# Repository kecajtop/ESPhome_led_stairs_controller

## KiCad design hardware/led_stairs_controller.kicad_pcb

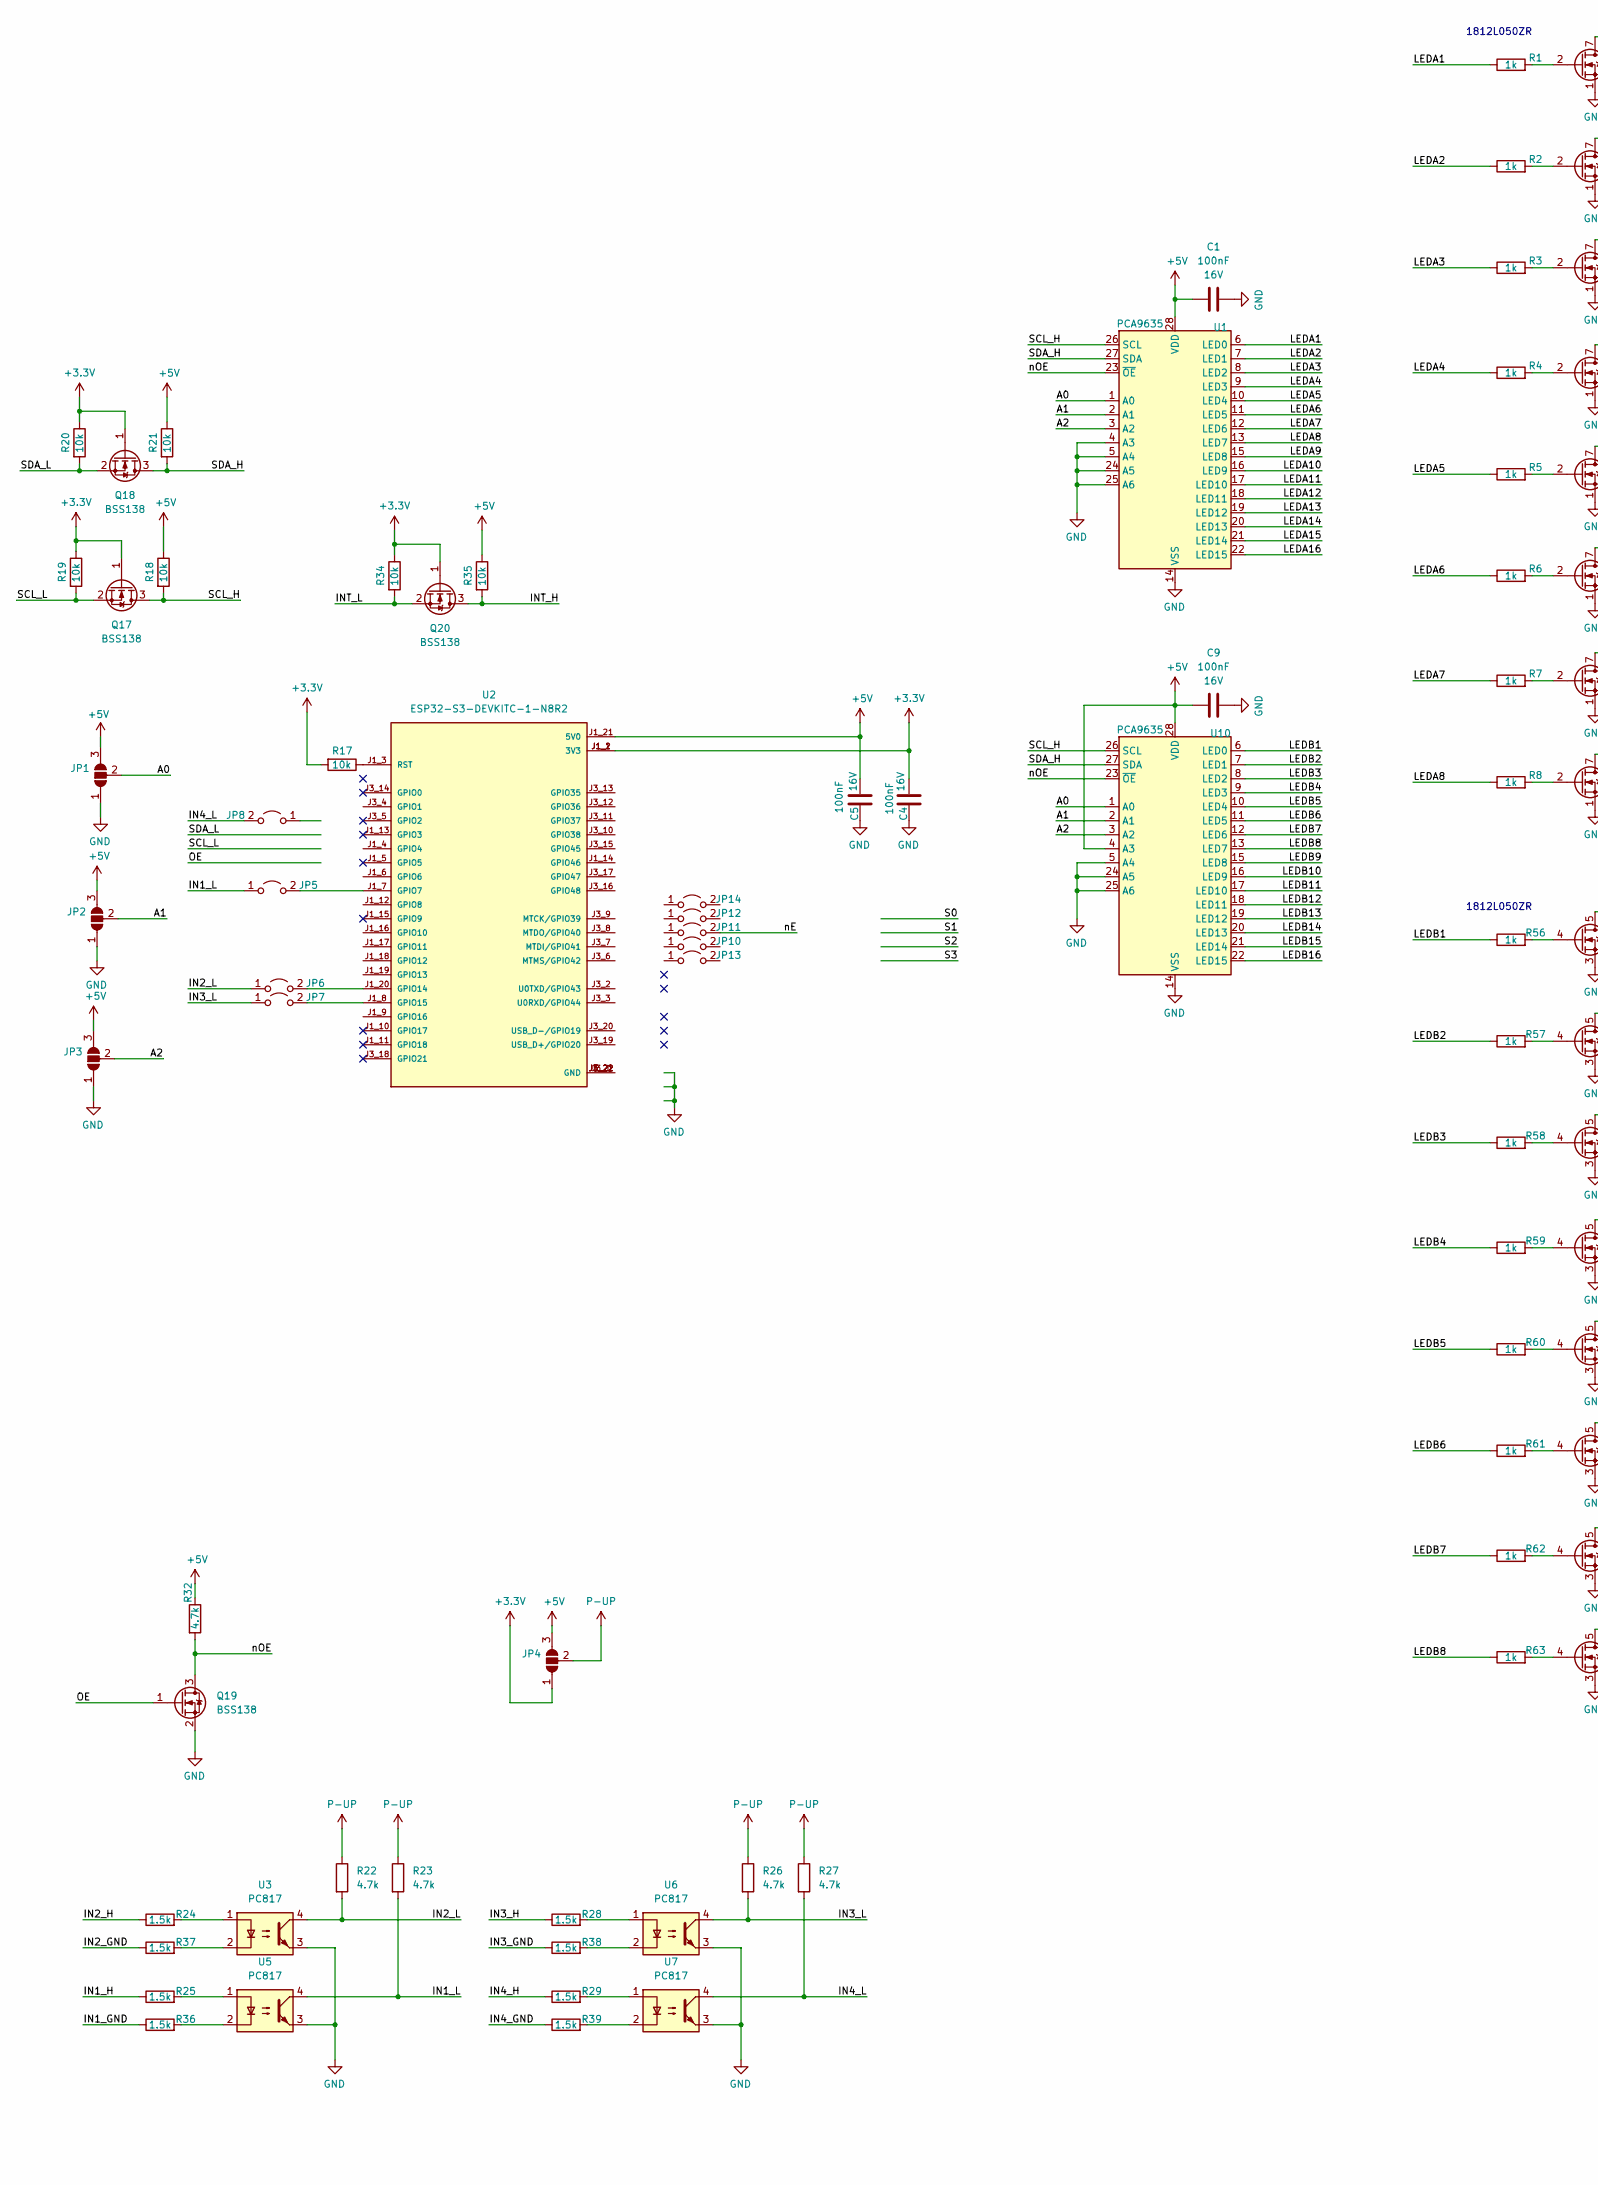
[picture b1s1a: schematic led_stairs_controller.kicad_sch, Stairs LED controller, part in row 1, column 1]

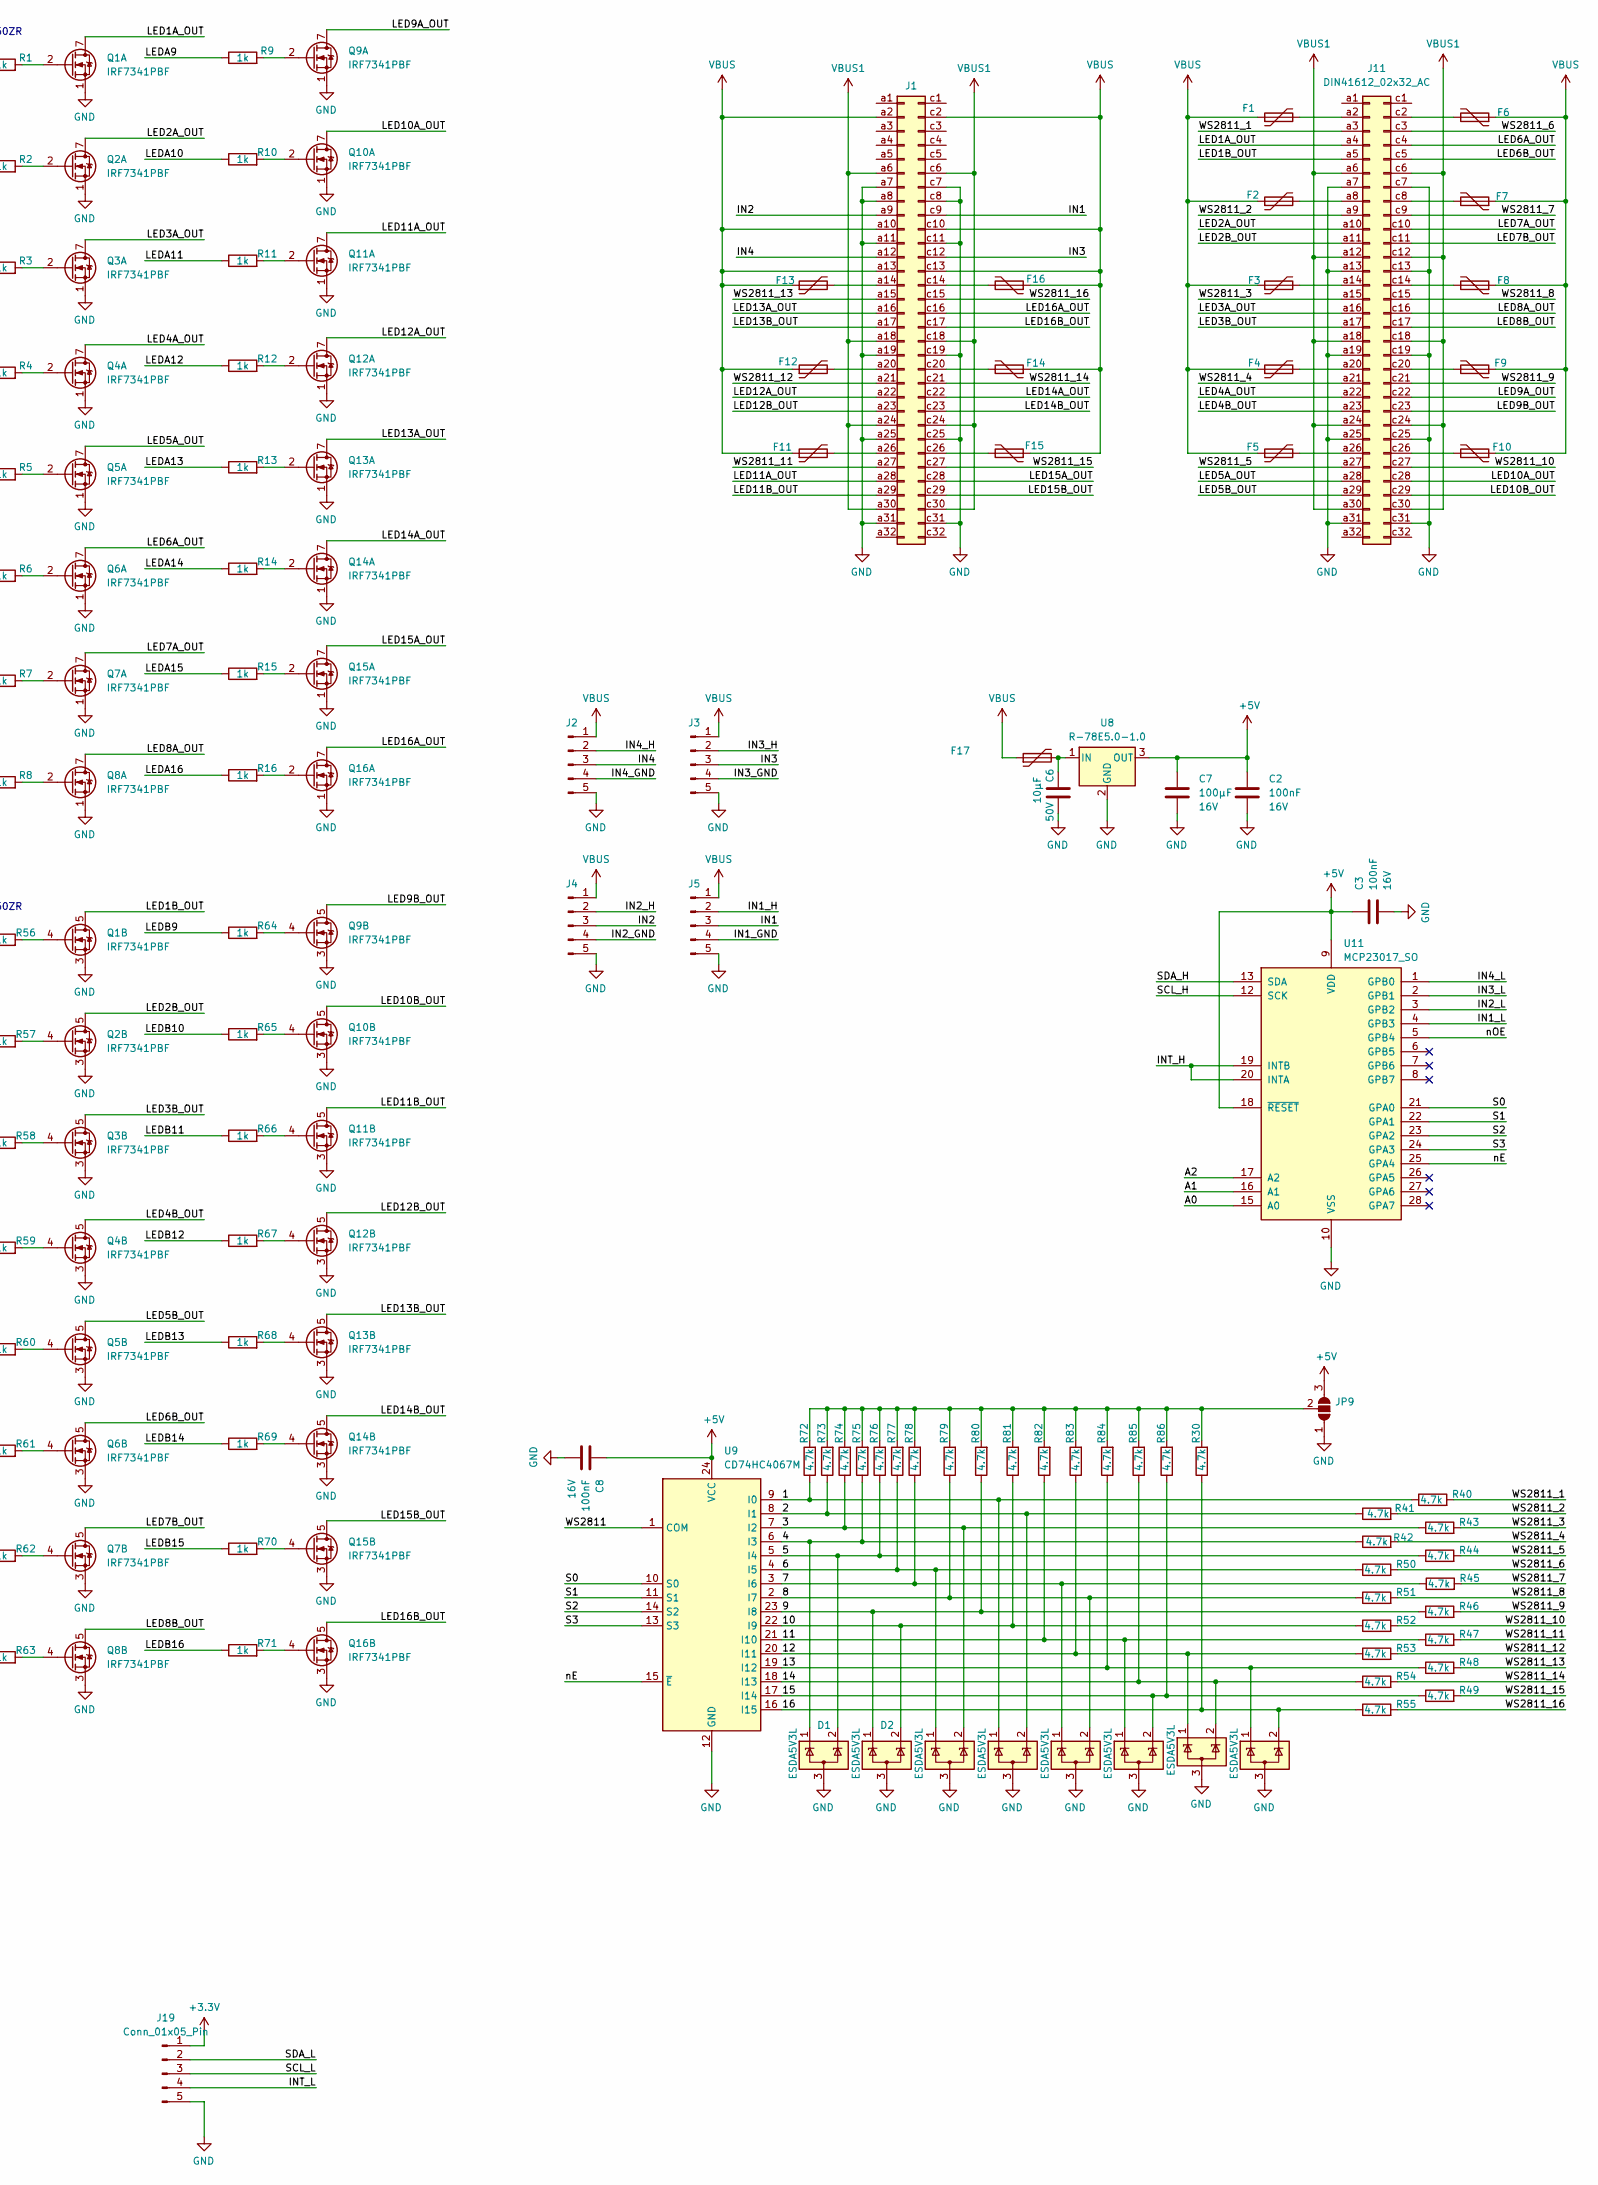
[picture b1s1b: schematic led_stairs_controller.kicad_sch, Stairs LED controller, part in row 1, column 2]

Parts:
C1, C2, C3, C4, C5, C8, C9: C0603_100nF_16V_X7R; C_0603_1608Metric; Voltage 16V; Manufacturer Part Number C0603C104J4RACTU; LCSC C14663
C6: C1210_10µF_50V_X5R; C_1210_3225Metric; Voltage 50V; Manufacturer Part Number C1210C106K5PAC7210; LCSC C13585
C7: C1210_100µF_16V_X5R; C_1210_3225Metric; Voltage 16V; Manufacturer Part Number C1210C107M4PAC7800; LCSC C15008
D1, D2, D3, D4, D5, D6, D7, D8: ESDA5V3L; SOT-23-3; LCSC C968007
F1, F2, F3, F4, F5, F6, F7, F8, F9, F10, F11, F12, F13, F14, F15, F16, F17: Polyfuse; Fuse_1812_4532Metric; LCSC C142747
J1, J11: DIN41612_02x32_AC; DIN41612_C_2x32_Male_Horizontal_THT
J2, J3, J4, J5: Conn_01x05_Pin; Jumper 5
J19: Conn_01x05_Pin; PinHeader_1x05_P2.54mm_Vertical
JP1, JP2, JP3, JP4, JP9: SolderJumper_3_Open; SolderJumper-3_P1.3mm_Open_RoundedPad1.0x1.5mm_NumberLabels
JP5, JP6, JP7, JP8, JP10, JP11, JP12, JP13, JP14: Jumper_2_Open; SolderJumper-2_P1.3mm_Open_RoundedPad1.0x1.5mm
Q1, Q2, Q3, Q4, Q5, Q6, Q7, Q8, Q9, Q10, Q11, Q12, Q13, Q14, Q15, Q16: IRF7341PBF; SOIC-8_3.9x4.9mm_P1.27mm
Q17, Q18, Q19, Q20: BSS138; SOT-23; LCSC C8545
R1, R2, R3, R4, R5, R6, R7, R8, R9, R10, R11, R12, R13, R14, R15, R16, R56, R57, R58, R59, R60, R61, R62, R63, R64, R65, R66, R67, R68, R69, R70, R71: R0603_1k_1%_100mW_100PPM_AC; R_0603_1608Metric; Manufacturer Part Number AC0603FR-071KL; LCSC C21190
R17, R18, R19, R20, R21, R34, R35: R0603_10k_1%_100mW_100PPM_AC; R_0603_1608Metric; Manufacturer Part Number AC0603FR-0710KL; LCSC C25804
R22, R23, R26, R27, R30, R32, R40, R41, R42, R43, R44, R45, R46, R47, R48, R49, R50, R51, R52, R53, R54, R55, R72, R73, R74, R75, R76, R77, R78, R79, R80, R81, R82, R83, R84, R85, R86: R0603_4.7k_1%_100mW_100PPM_AC; R_0603_1608Metric; Manufacturer Part Number AC0603FR-074K7L; LCSC C23162
R24, R25, R28, R29, R36, R37, R38, R39: R0805_1.5k_1%_125mW_100PPM_AC; R_0805_2012Metric; Manufacturer Part Number AC0805FR-071K5L; LCSC C22843
U1, U10: PCA9635; TSSOP-28_4.4x9.7mm_P0.65mm; LCSC C110795
U2: ESP32-S3-DEVKITC-1-N8R2; XCVR_ESP32-S3-DEVKITC-1-N8R2; PARTREV V1
U3, U5, U6, U7: PC817; DIP-4_W7.62mm; LCSC C109225
U8: R-78E5.0-1.0; Converter_DCDC_RECOM_R-78E-0.5_THT
U9: CD74HC4067M; SOIC-24W_7.5x15.4mm_P1.27mm
U11: MCP23017_SO; SOIC-28W_7.5x17.9mm_P1.27mm

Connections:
+3.3V: C4.1, J19.1, JP4.1 (A), Q17.1 (G), Q18.1 (G), Q20.1 (G), R17.2, R19.1, R20.1, R34.1, U2.J1_1 (3V3), U2.J1_2 (3V3)
+5V: C1.1, C2.2, C3.2, C5.1, C7.1, C8.2, C9.1, JP1.3 (B), JP2.3 (B), JP3.3 (B), JP4.3 (B), JP9.3 (B), R18.1, R21.1, R32.1, R35.1, U1.28 (VDD), U2.J1_21 (5V0), U8.3 (OUT), U9.24 (VCC), U10.4 (A3), U10.28 (VDD), U11.9 (VDD), U11.18 (~RESET)
/1: D4.1 (K), R40.1, R72.1, U9.9 (I0)
/2: D4.2 (K), R41.1, R73.1, U9.8 (I1)
/3: D3.2 (K), R43.1, R74.1, U9.7 (I2)
/4: D1.1 (K), R42.1, R75.1, U9.6 (I3)
/5: D1.2 (K), R44.1, R76.1, U9.5 (I4)
/6: D3.1 (K), R50.1, R77.1, U9.4 (I5)
/7: D5.1 (K), R45.1, R78.1, U9.3 (I6)
/8: D5.2 (K), R51.1, R79.1, U9.2 (I7)
/9: D2.1 (K), R46.1, R80.1, U9.23 (I8)
/10: D2.2 (K), R52.1, R81.1, U9.22 (I9)
/11: D6.1 (K), R47.1, R82.1, U9.21 (I10)
/12: D7.1 (K), R53.1, R83.1, U9.20 (I11)
/13: D8.1 (K), R48.1, R84.1, U9.19 (I12)
/14: D7.2 (K), R54.1, R85.1, U9.18 (I13)
/15: D6.2 (K), R49.1, R86.1, U9.17 (I14)
/16: D8.2 (K), R30.1, R55.1, U9.16 (I15)
/A0: JP1.2 (C), U1.1 (A0), U10.1 (A0), U11.15 (A0)
/A1: JP2.2 (C), U1.2 (A1), U10.2 (A1), U11.16 (A1)
/A2: JP3.2 (C), U1.3 (A2), U10.3 (A2), U11.17 (A2)
/IN1: J1.c9, J5.3
/IN1_GND: J5.4, R36.1
/IN1_H: J5.2, R25.1
/IN1_L: JP5.1 (A), R23.2, U5.4, U11.4 (GPB3)
/IN2: J1.a9, J4.3
/IN2_GND: J4.4, R37.1
/IN2_H: J4.2, R24.1
/IN2_L: JP6.1 (A), R22.2, U3.4, U11.3 (GPB2)
/IN3: J1.c12, J3.3
/IN3_GND: J3.4, R38.1
/IN3_H: J3.2, R28.1
/IN3_L: JP7.1 (A), R26.2, U6.4, U11.2 (GPB1)
/IN4: J1.a12, J2.3
/IN4_GND: J2.4, R39.1
/IN4_H: J2.2, R29.1
/IN4_L: JP8.2 (B), R27.2, U7.4, U11.1 (GPB0)
/INT_H: Q20.3 (D), R35.2, U11.19 (INTB), U11.20 (INTA)
/INT_L: J19.4, Q20.2 (S), R34.2
/LED1A_OUT: J11.a4, Q1.7 (D1), Q1.8 (D1)
/LED1B_OUT: J11.a5, Q1.5 (D2), Q1.6 (D2)
/LED2A_OUT: J11.a10, Q2.7 (D1), Q2.8 (D1)
/LED2B_OUT: J11.a11, Q2.5 (D2), Q2.6 (D2)
/LED3A_OUT: J11.a16, Q3.7 (D1), Q3.8 (D1)
/LED3B_OUT: J11.a17, Q3.5 (D2), Q3.6 (D2)
/LED4A_OUT: J11.a22, Q4.7 (D1), Q4.8 (D1)
/LED4B_OUT: J11.a23, Q4.5 (D2), Q4.6 (D2)
/LED5A_OUT: J11.a28, Q5.7 (D1), Q5.8 (D1)
/LED5B_OUT: J11.a29, Q5.5 (D2), Q5.6 (D2)
/LED6A_OUT: J11.c4, Q6.7 (D1), Q6.8 (D1)
/LED6B_OUT: J11.c5, Q6.5 (D2), Q6.6 (D2)
/LED7A_OUT: J11.c10, Q7.7 (D1), Q7.8 (D1)
/LED7B_OUT: J11.c11, Q7.5 (D2), Q7.6 (D2)
/LED8A_OUT: J11.c16, Q8.7 (D1), Q8.8 (D1)
/LED8B_OUT: J11.c17, Q8.5 (D2), Q8.6 (D2)
/LED9A_OUT: J11.c22, Q9.7 (D1), Q9.8 (D1)
/LED9B_OUT: J11.c23, Q9.5 (D2), Q9.6 (D2)
/LED10A_OUT: J11.c28, Q10.7 (D1), Q10.8 (D1)
/LED10B_OUT: J11.c29, Q10.5 (D2), Q10.6 (D2)
/LED11A_OUT: J1.a28, Q11.7 (D1), Q11.8 (D1)
/LED11B_OUT: J1.a29, Q11.5 (D2), Q11.6 (D2)
/LED12A_OUT: J1.a22, Q12.7 (D1), Q12.8 (D1)
/LED12B_OUT: J1.a23, Q12.5 (D2), Q12.6 (D2)
/LED13A_OUT: J1.a16, Q13.7 (D1), Q13.8 (D1)
/LED13B_OUT: J1.a17, Q13.5 (D2), Q13.6 (D2)
/LED14A_OUT: J1.c22, Q14.7 (D1), Q14.8 (D1)
/LED14B_OUT: J1.c23, Q14.5 (D2), Q14.6 (D2)
/LED15A_OUT: J1.c28, Q15.7 (D1), Q15.8 (D1)
/LED15B_OUT: J1.c29, Q15.5 (D2), Q15.6 (D2)
/LED16A_OUT: J1.c16, Q16.7 (D1), Q16.8 (D1)
/LED16B_OUT: J1.c17, Q16.5 (D2), Q16.6 (D2)
/LEDA1: R1.1, U1.6 (LED0)
/LEDA2: R2.1, U1.7 (LED1)
/LEDA3: R3.1, U1.8 (LED2)
/LEDA4: R4.1, U1.9 (LED3)
/LEDA5: R5.1, U1.10 (LED4)
/LEDA6: R6.1, U1.11 (LED5)
/LEDA7: R7.1, U1.12 (LED6)
/LEDA8: R8.1, U1.13 (LED7)
/LEDA9: R9.1, U1.15 (LED8)
/LEDA10: R10.1, U1.16 (LED9)
/LEDA11: R11.1, U1.17 (LED10)
/LEDA12: R12.1, U1.18 (LED11)
/LEDA13: R13.1, U1.19 (LED12)
/LEDA14: R14.1, U1.20 (LED13)
/LEDA15: R15.1, U1.21 (LED14)
/LEDA16: R16.1, U1.22 (LED15)
/LEDB1: R56.1, U10.6 (LED0)
/LEDB2: R57.1, U10.7 (LED1)
/LEDB3: R58.1, U10.8 (LED2)
/LEDB4: R59.1, U10.9 (LED3)
/LEDB5: R60.1, U10.10 (LED4)
/LEDB6: R61.1, U10.11 (LED5)
/LEDB7: R62.1, U10.12 (LED6)
/LEDB8: R63.1, U10.13 (LED7)
/LEDB9: R64.1, U10.15 (LED8)
/LEDB10: R65.1, U10.16 (LED9)
/LEDB11: R66.1, U10.17 (LED10)
/LEDB12: R67.1, U10.18 (LED11)
/LEDB13: R68.1, U10.19 (LED12)
/LEDB14: R69.1, U10.20 (LED13)
/LEDB15: R70.1, U10.21 (LED14)
/LEDB16: R71.1, U10.22 (LED15)
/OE: Q19.1 (G)
/S0: U9.10 (S0), U11.21 (GPA0)
/S1: U9.11 (S1), U11.22 (GPA1)
/S2: U9.14 (S2), U11.23 (GPA2)
/S3: U9.13 (S3), U11.24 (GPA3)
/SCL_H: Q17.3 (D), R18.2, U1.26 (SCL), U10.26 (SCL), U11.12 (SCK)
/SCL_L: J19.3, Q17.2 (S), R19.2
/SDA_H: Q18.3 (D), R21.2, U1.27 (SDA), U10.27 (SDA), U11.13 (SDA)
/SDA_L: J19.2, Q18.2 (S), R20.2
/WS2811: U9.1 (COM)
/WS2811_1: J11.a3, R40.2
/WS2811_2: J11.a9, R41.2
/WS2811_3: J11.a15, R43.2
/WS2811_4: J11.a21, R42.2
/WS2811_5: J11.a27, R44.2
/WS2811_6: J11.c3, R50.2
/WS2811_7: J11.c9, R45.2
/WS2811_8: J11.c15, R51.2
/WS2811_9: J11.c21, R46.2
/WS2811_10: J11.c27, R52.2
/WS2811_11: J1.a27, R47.2
/WS2811_12: J1.a21, R53.2
/WS2811_13: J1.a15, R48.2
/WS2811_14: J1.c21, R54.2
/WS2811_15: J1.c27, R49.2
/WS2811_16: J1.c15, R55.2
/nE: JP11.2 (B), U9.15 (~E), U11.25 (GPA4)
/nOE: Q19.3 (D), R32.2, U1.23 (~OE), U10.23 (~OE), U11.5 (GPB4)
GND: C1.2, C2.1, C3.1, C4.2, C5.2, C6.2, C7.2, C8.1, C9.2, D1.3 (A), D2.3 (A), D3.3 (A), D4.3 (A), D5.3 (A), D6.3 (A), D7.3 (A), D8.3 (A), J1.a7, J1.a8, J1.a11, J1.a19, J1.a25, J1.a31, J1.c7, J1.c8, J1.c11, J1.c19, J1.c25, J1.c31, J2.5, J3.5, J4.5, J5.5, J11.a7, J11.a13, J11.a19, J11.a25, J11.a31, J11.c7, J11.c13, J11.c19, J11.c25, J11.c31, J19.5, JP1.1 (A), JP2.1 (A), JP3.1 (A), JP9.1 (A), Q1.1 (S1), Q1.3 (S2), Q2.1 (S1), Q2.3 (S2), Q3.1 (S1), Q3.3 (S2), Q4.1 (S1), Q4.3 (S2), Q5.1 (S1), Q5.3 (S2), Q6.1 (S1), Q6.3 (S2), Q7.1 (S1), Q7.3 (S2), Q8.1 (S1), Q8.3 (S2), Q9.1 (S1), Q9.3 (S2), Q10.1 (S1), Q10.3 (S2), Q11.1 (S1), Q11.3 (S2), Q12.1 (S1), Q12.3 (S2), Q13.1 (S1), Q13.3 (S2), Q14.1 (S1), Q14.3 (S2), Q15.1 (S1), Q15.3 (S2), Q16.1 (S1), Q16.3 (S2), Q19.2 (S), U1.4 (A3), U1.5 (A4), U1.14 (VSS), U1.24 (A5), U1.25 (A6), U3.3, U5.3, U6.3, U7.3, U8.2 (GND), U9.12 (GND), U10.5 (A4), U10.14 (VSS), U10.24 (A5), U10.25 (A6), U11.10 (VSS)
unnamed: F13.2, J1.a14
unnamed: F12.2, J1.a20
unnamed: F11.2, J1.a26
unnamed: F16.2, J1.c14
unnamed: F14.2, J1.c20
unnamed: F15.2, J1.c26
unnamed: F1.2, J11.a2
unnamed: F2.2, J11.a8
unnamed: F3.2, J11.a14
unnamed: F4.2, J11.a20
unnamed: F5.2, J11.a26
unnamed: F6.2, J11.c2
unnamed: F7.2, J11.c8
unnamed: F8.2, J11.c14
unnamed: F9.2, J11.c20
unnamed: F10.2, J11.c26
unnamed: JP5.2 (B), U2.J1_7 (GPIO7)
unnamed: JP6.2 (B), U2.J1_20 (GPIO14)
unnamed: JP7.2 (B), U2.J1_8 (GPIO15)
unnamed: JP9.2 (C), R30.2, R72.2, R73.2, R74.2, R75.2, R76.2, R77.2, R78.2, R79.2, R80.2, R81.2, R82.2, R83.2, R84.2, R85.2, R86.2
unnamed: Q1.2 (G1), R1.2
unnamed: Q1.4 (G2), R56.2
unnamed: Q2.2 (G1), R2.2
unnamed: Q2.4 (G2), R57.2
unnamed: Q3.2 (G1), R3.2
unnamed: Q3.4 (G2), R58.2
unnamed: Q4.2 (G1), R4.2
unnamed: Q4.4 (G2), R59.2
unnamed: Q5.2 (G1), R5.2
unnamed: Q5.4 (G2), R60.2
unnamed: Q6.2 (G1), R6.2
unnamed: Q6.4 (G2), R61.2
unnamed: Q7.2 (G1), R7.2
unnamed: Q7.4 (G2), R62.2
unnamed: Q8.2 (G1), R8.2
unnamed: Q8.4 (G2), R63.2
unnamed: Q9.2 (G1), R9.2
unnamed: Q9.4 (G2), R64.2
unnamed: Q10.2 (G1), R10.2
unnamed: Q10.4 (G2), R65.2
unnamed: Q11.2 (G1), R11.2
unnamed: Q11.4 (G2), R66.2
unnamed: Q12.2 (G1), R12.2
unnamed: Q12.4 (G2), R67.2
unnamed: Q13.2 (G1), R13.2
unnamed: Q13.4 (G2), R68.2
unnamed: Q14.2 (G1), R14.2
unnamed: Q14.4 (G2), R69.2
unnamed: Q15.2 (G1), R15.2
unnamed: Q15.4 (G2), R70.2
unnamed: Q16.2 (G1), R16.2
unnamed: Q16.4 (G2), R71.2
unnamed: R24.2, U3.1
unnamed: R25.2, U5.1
unnamed: R28.2, U6.1
unnamed: R29.2, U7.1
unnamed: R36.2, U5.2
unnamed: R37.2, U3.2
unnamed: R38.2, U6.2
unnamed: R39.2, U7.2
unnamed: R17.1, U2.J1_3 (RST)
unnamed: C6.1, F17.2, U8.1 (IN)
P-UP: JP4.2 (C), R22.1, R23.1, R26.1, R27.1
VBUS: F1.1, F2.1, F3.1, F4.1, F5.1, F6.1, F7.1, F8.1, F9.1, F10.1, F11.1, F12.1, F13.1, F14.1, F15.1, F16.1, F17.1, J1.a2, J1.a10, J1.a13, J1.c2, J1.c10, J1.c13, J2.1, J3.1, J4.1, J5.1
VBUS1: J1.a6, J1.a18, J1.a24, J1.a30, J1.c6, J1.c18, J1.c24, J1.c30, J11.a6, J11.a12, J11.a18, J11.a24, J11.a30, J11.c6, J11.c12, J11.c18, J11.c24, J11.c30

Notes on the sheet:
1812L050ZR

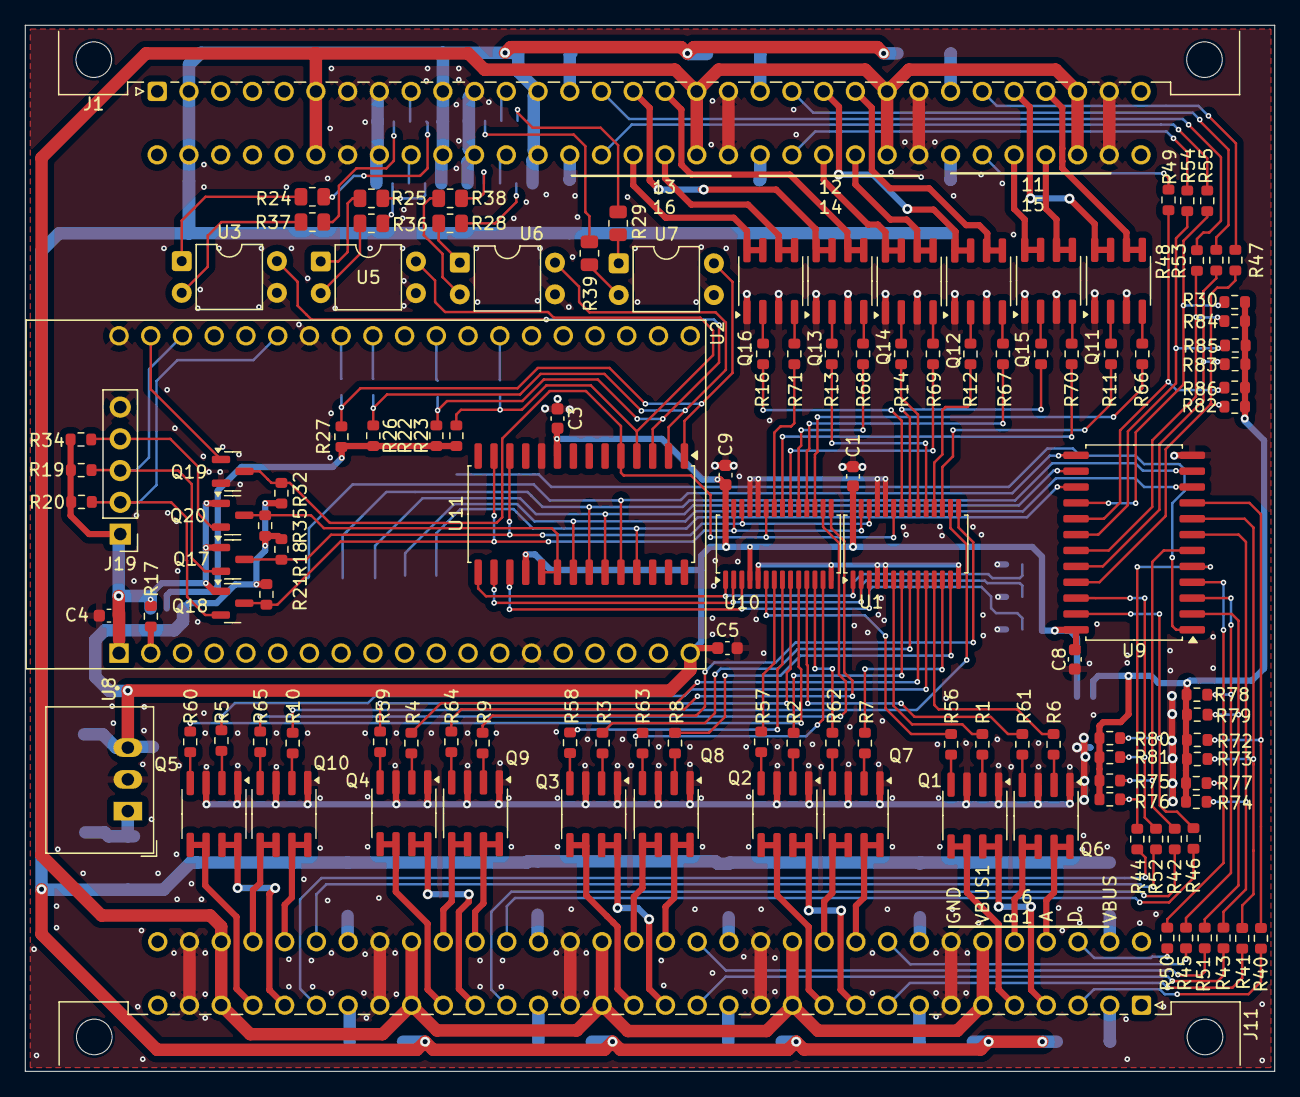
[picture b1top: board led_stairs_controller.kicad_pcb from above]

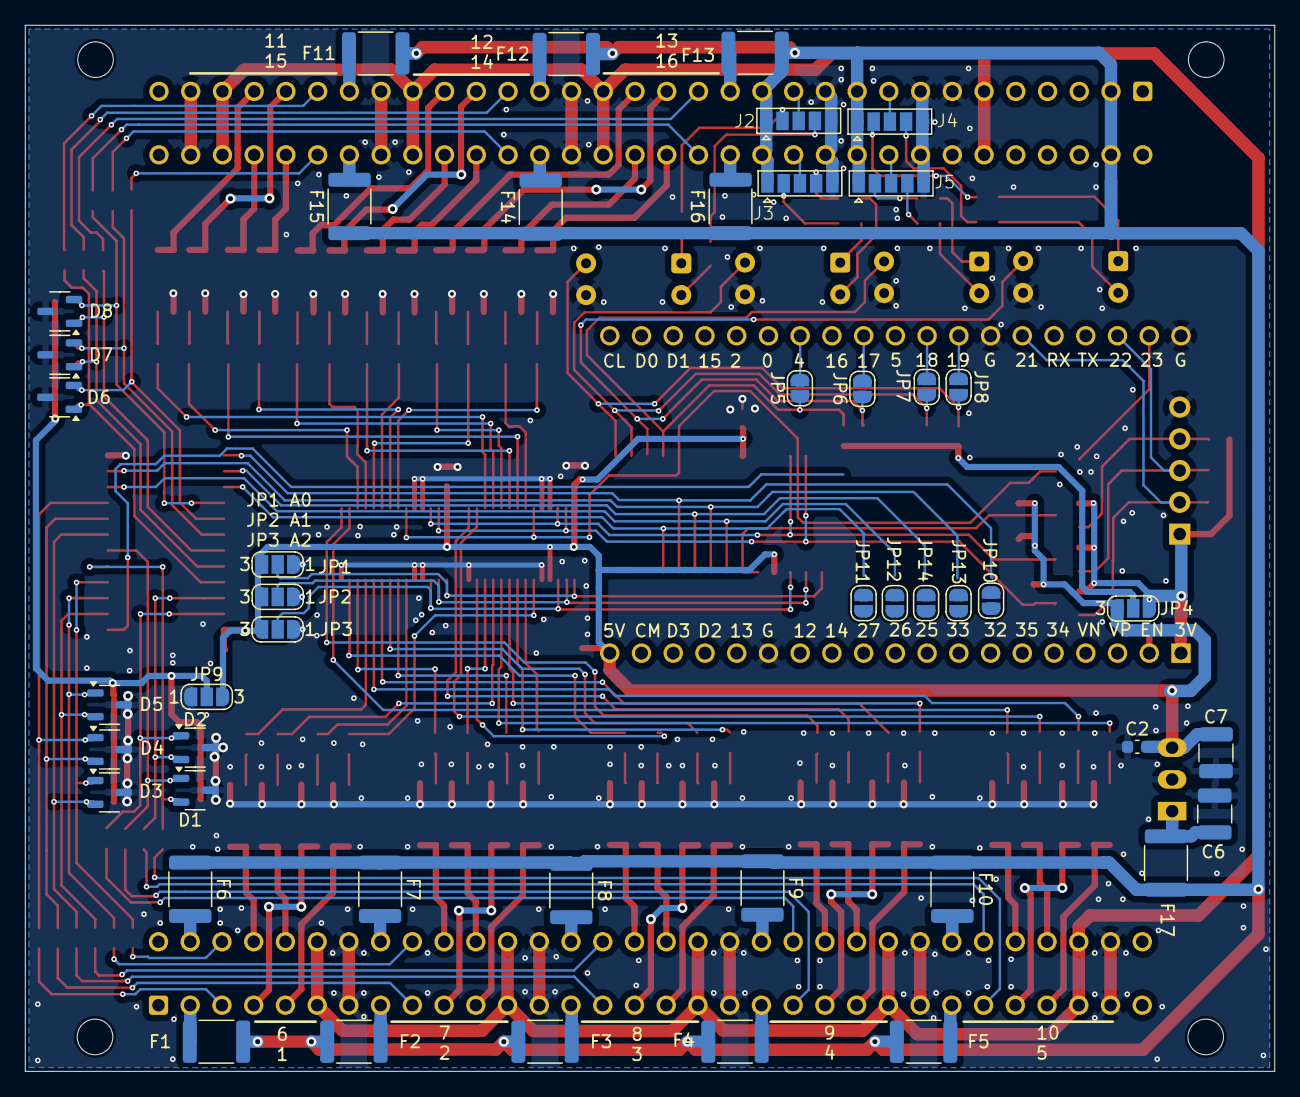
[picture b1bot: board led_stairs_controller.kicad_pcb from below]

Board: 2 copper layers, 100.0 x 83.7 mm, 169 parts (46 on the bottom side), 191 nets.

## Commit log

2024-02-02 Initial commit
    Initial commit
2024-02-02 update
    update
2024-08-19 step file added
